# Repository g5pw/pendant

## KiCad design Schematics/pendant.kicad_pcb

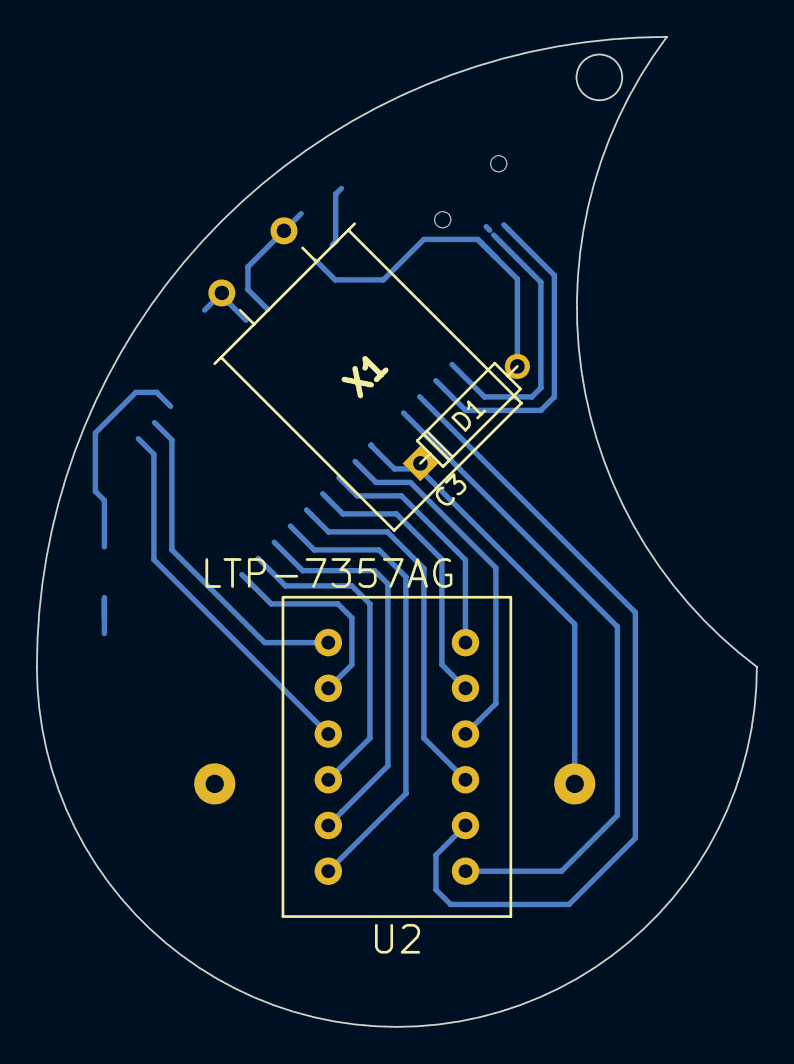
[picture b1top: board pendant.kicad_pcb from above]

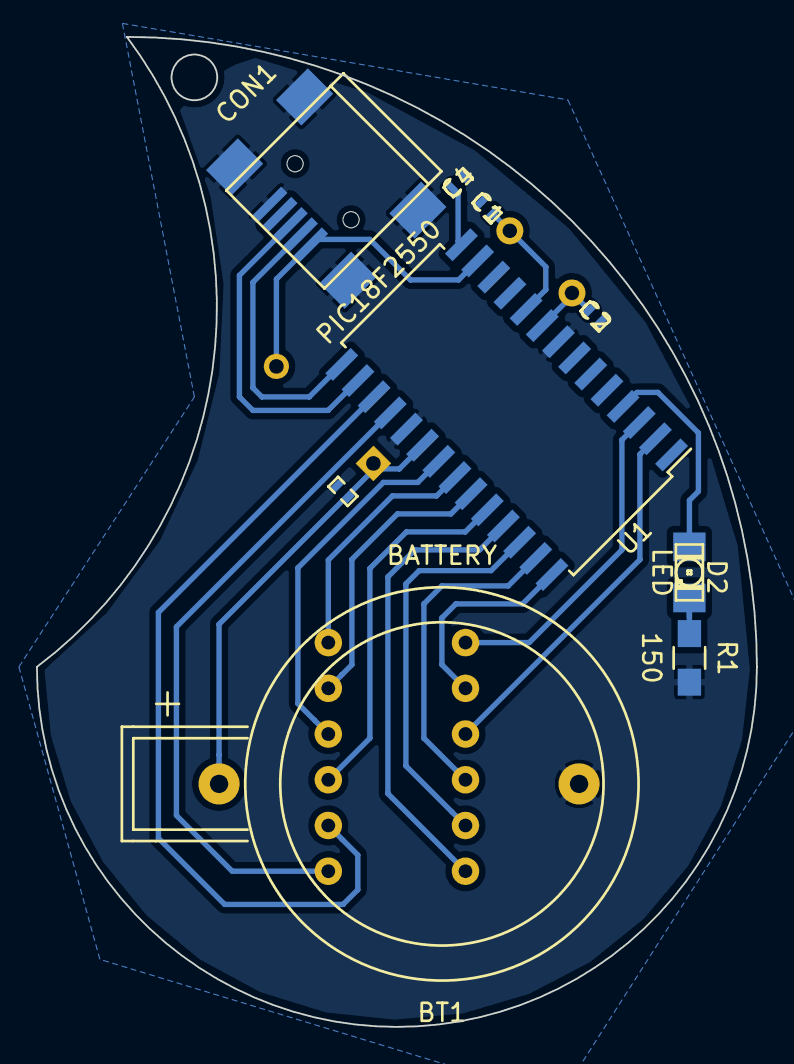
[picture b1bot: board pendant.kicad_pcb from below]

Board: 2 copper layers, 40.0 x 55.0 mm, 12 parts (9 on the bottom side), 22 nets.

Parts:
BT1: BATTERY; CR2032H
C1, C2: 22p; SMD-0402
C3, C4: 100n; SMD-0402
CON1: USB-MINI-B; USB_Mini-B
D1: DIODESCH; D3
D2: LED; LED-1206
R1: 150; R_0805_HandSoldering
U1: PIC18F2550; SOIC-28_7.5x17.9mm_Pitch1.27mm
U2: LTP-7357AG
X1: CRYSTAL; Crystal_HC49-U_Horizontal_Typ1

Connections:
/Col1: U1.3, U2.1
/Col2: U1.2, U2.3
/Col3: U1.21, U2.10
/Col4: U1.18, U2.7
/Col5: U1.17, U2.8
/Row1: U1.22, U2.12
/Row2: U1.23, U2.11
/Row3: U1.28, U2.2
/Row4: U1.24, U2.9
/Row5: U1.27, U2.4
/Row6: U1.26, U2.5
/Row7: U1.25, U2.6
/UsbSense: CON1.1, D1.1, U1.13
GND: BT1.2, C1.2, C2.2, C3.2, C4.2, CON1.5, CON1.6, CON1.7, CON1.8, CON1.9, R1.2, U1.8, U1.19
unnamed: C1.1, U1.10, X1.1
unnamed: C2.1, U1.9, X1.2
unnamed: C4.1, U1.14
unnamed: CON1.2, U1.15
unnamed: CON1.3, U1.16
unnamed: D2.1, U1.4
unnamed: D2.2, R1.1
VDD: BT1.1, C3.1, D1.2, U1.20

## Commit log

2014-12-24 Add v1 schematics
2014-12-24 Add v1 code, too
2014-12-24 Add gitignore to exclude extra nbproject files
